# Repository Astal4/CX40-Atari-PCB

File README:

You've landed on a CX40 replacement board project! Well there's not much here right now but the eventual goals are to have Joy2B+ supporting PCBs which can fit inside of a CX40/CX40 clone housing, with upgraded, nicer feeling tactile switches instead of the CX40's original metal domes.

Current goals...

~~1. CX40 Drop in replacement board~~
2. Making positioning during install process less tedious
3. Joy2B+ Support and other enhancements

Current phase is pre-alpha, there is not a working prototype yet. I will be uploading prototypes here and marking them as so, and will label a release board. Potential upgrades in the future could include debouncing.

The project is licensed under the MIT license.

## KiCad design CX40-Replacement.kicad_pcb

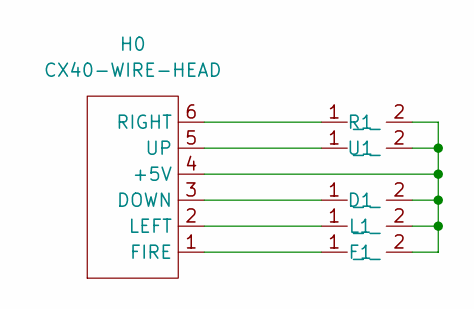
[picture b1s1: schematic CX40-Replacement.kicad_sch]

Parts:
D1: Button
F1: Button
H0: CX40-WIRE-HEAD; CableBreakout
L1: Button
R1: Button
U1: Button

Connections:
unnamed: D1.1 (_), H0.3 (DOWN)
unnamed: D1.2 (_), F1.2 (_), H0.4 (+5V), L1.2 (_), R1.2 (_), U1.2 (_)
unnamed: F1.1 (_), H0.1 (FIRE)
unnamed: H0.2 (LEFT), L1.1 (_)
unnamed: H0.5 (UP), U1.1 (_)
unnamed: H0.6 (RIGHT), R1.1 (_)

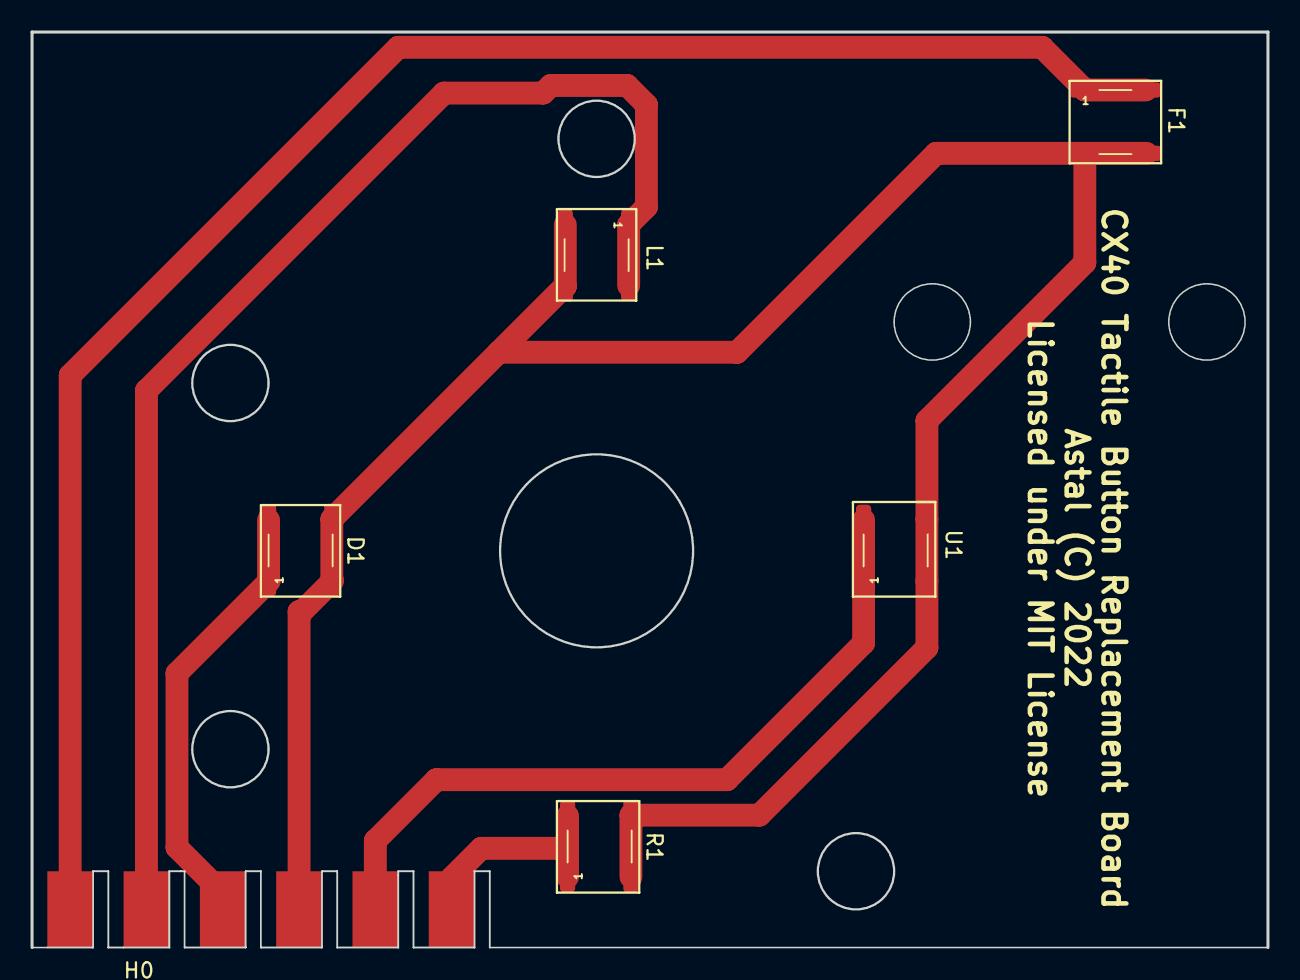
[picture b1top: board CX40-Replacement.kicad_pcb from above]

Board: 2 copper layers, 81.0 x 60.0 mm, 6 parts (0 on the bottom side), 6 nets.

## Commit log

2022-10-16 Add BOM spreadsheet
2022-10-26 Enlarge Solder Pads
2023-01-01 New Repo

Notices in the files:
CX40-Replacement.kicad_pcb:
Astal (C) 2022
Licensed under MIT License
